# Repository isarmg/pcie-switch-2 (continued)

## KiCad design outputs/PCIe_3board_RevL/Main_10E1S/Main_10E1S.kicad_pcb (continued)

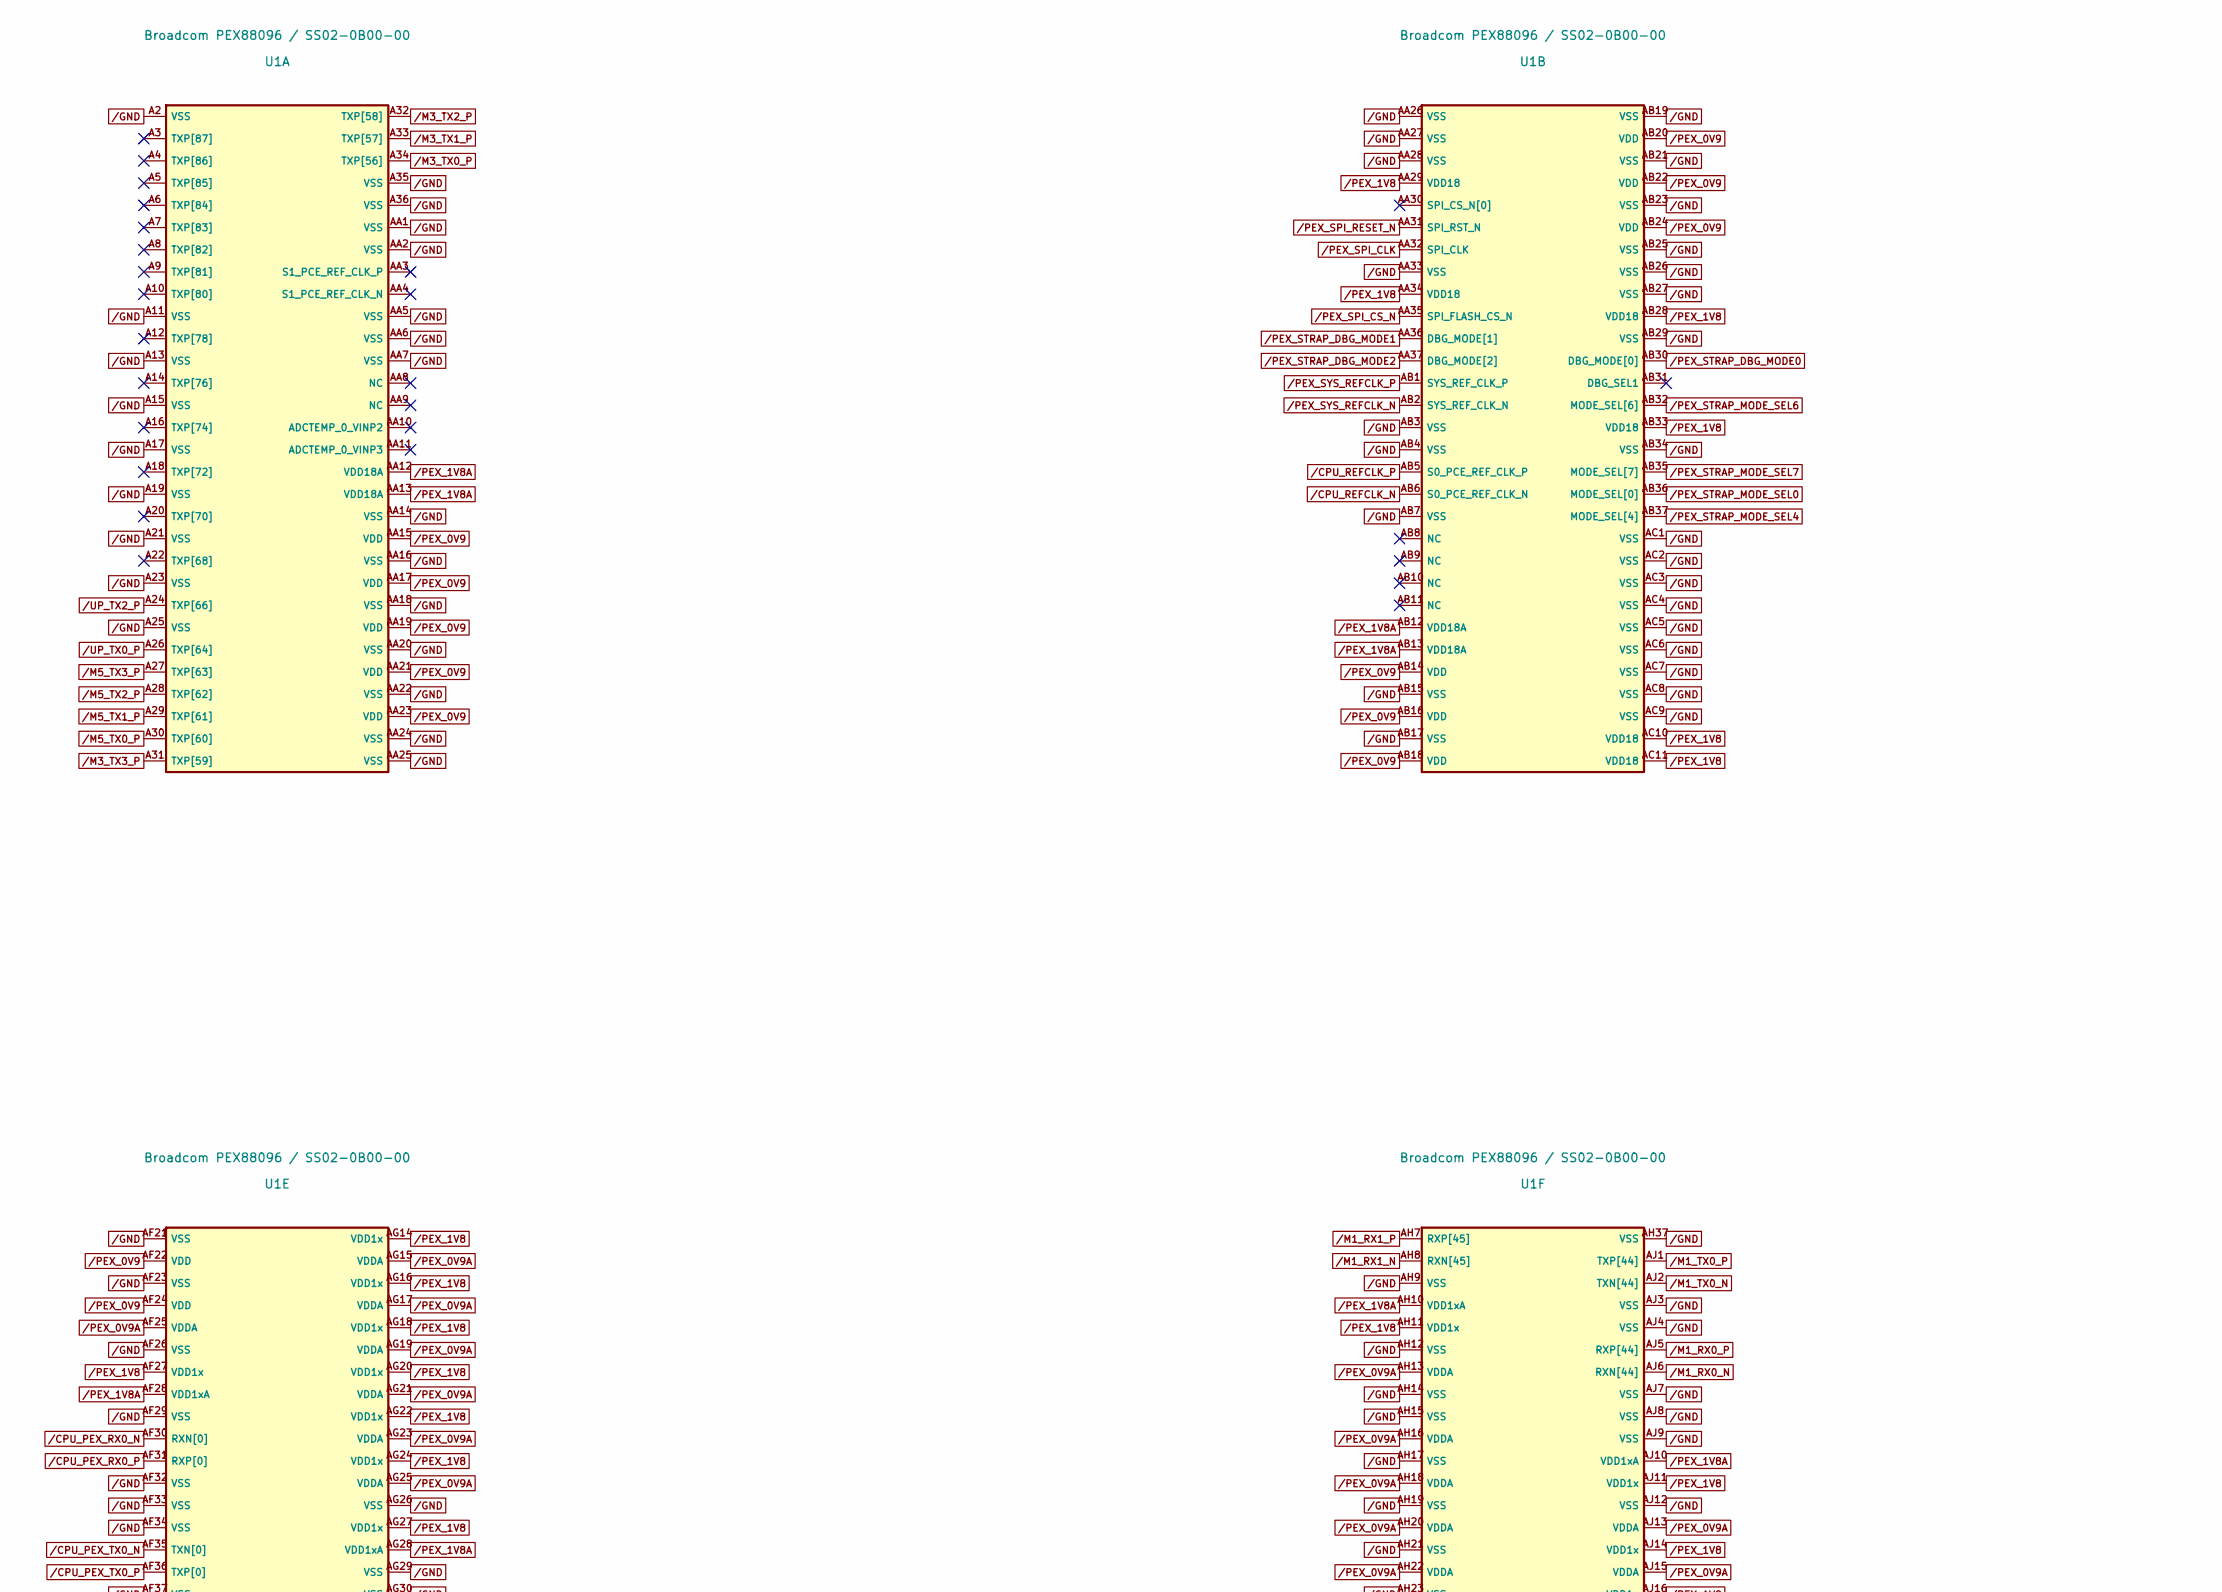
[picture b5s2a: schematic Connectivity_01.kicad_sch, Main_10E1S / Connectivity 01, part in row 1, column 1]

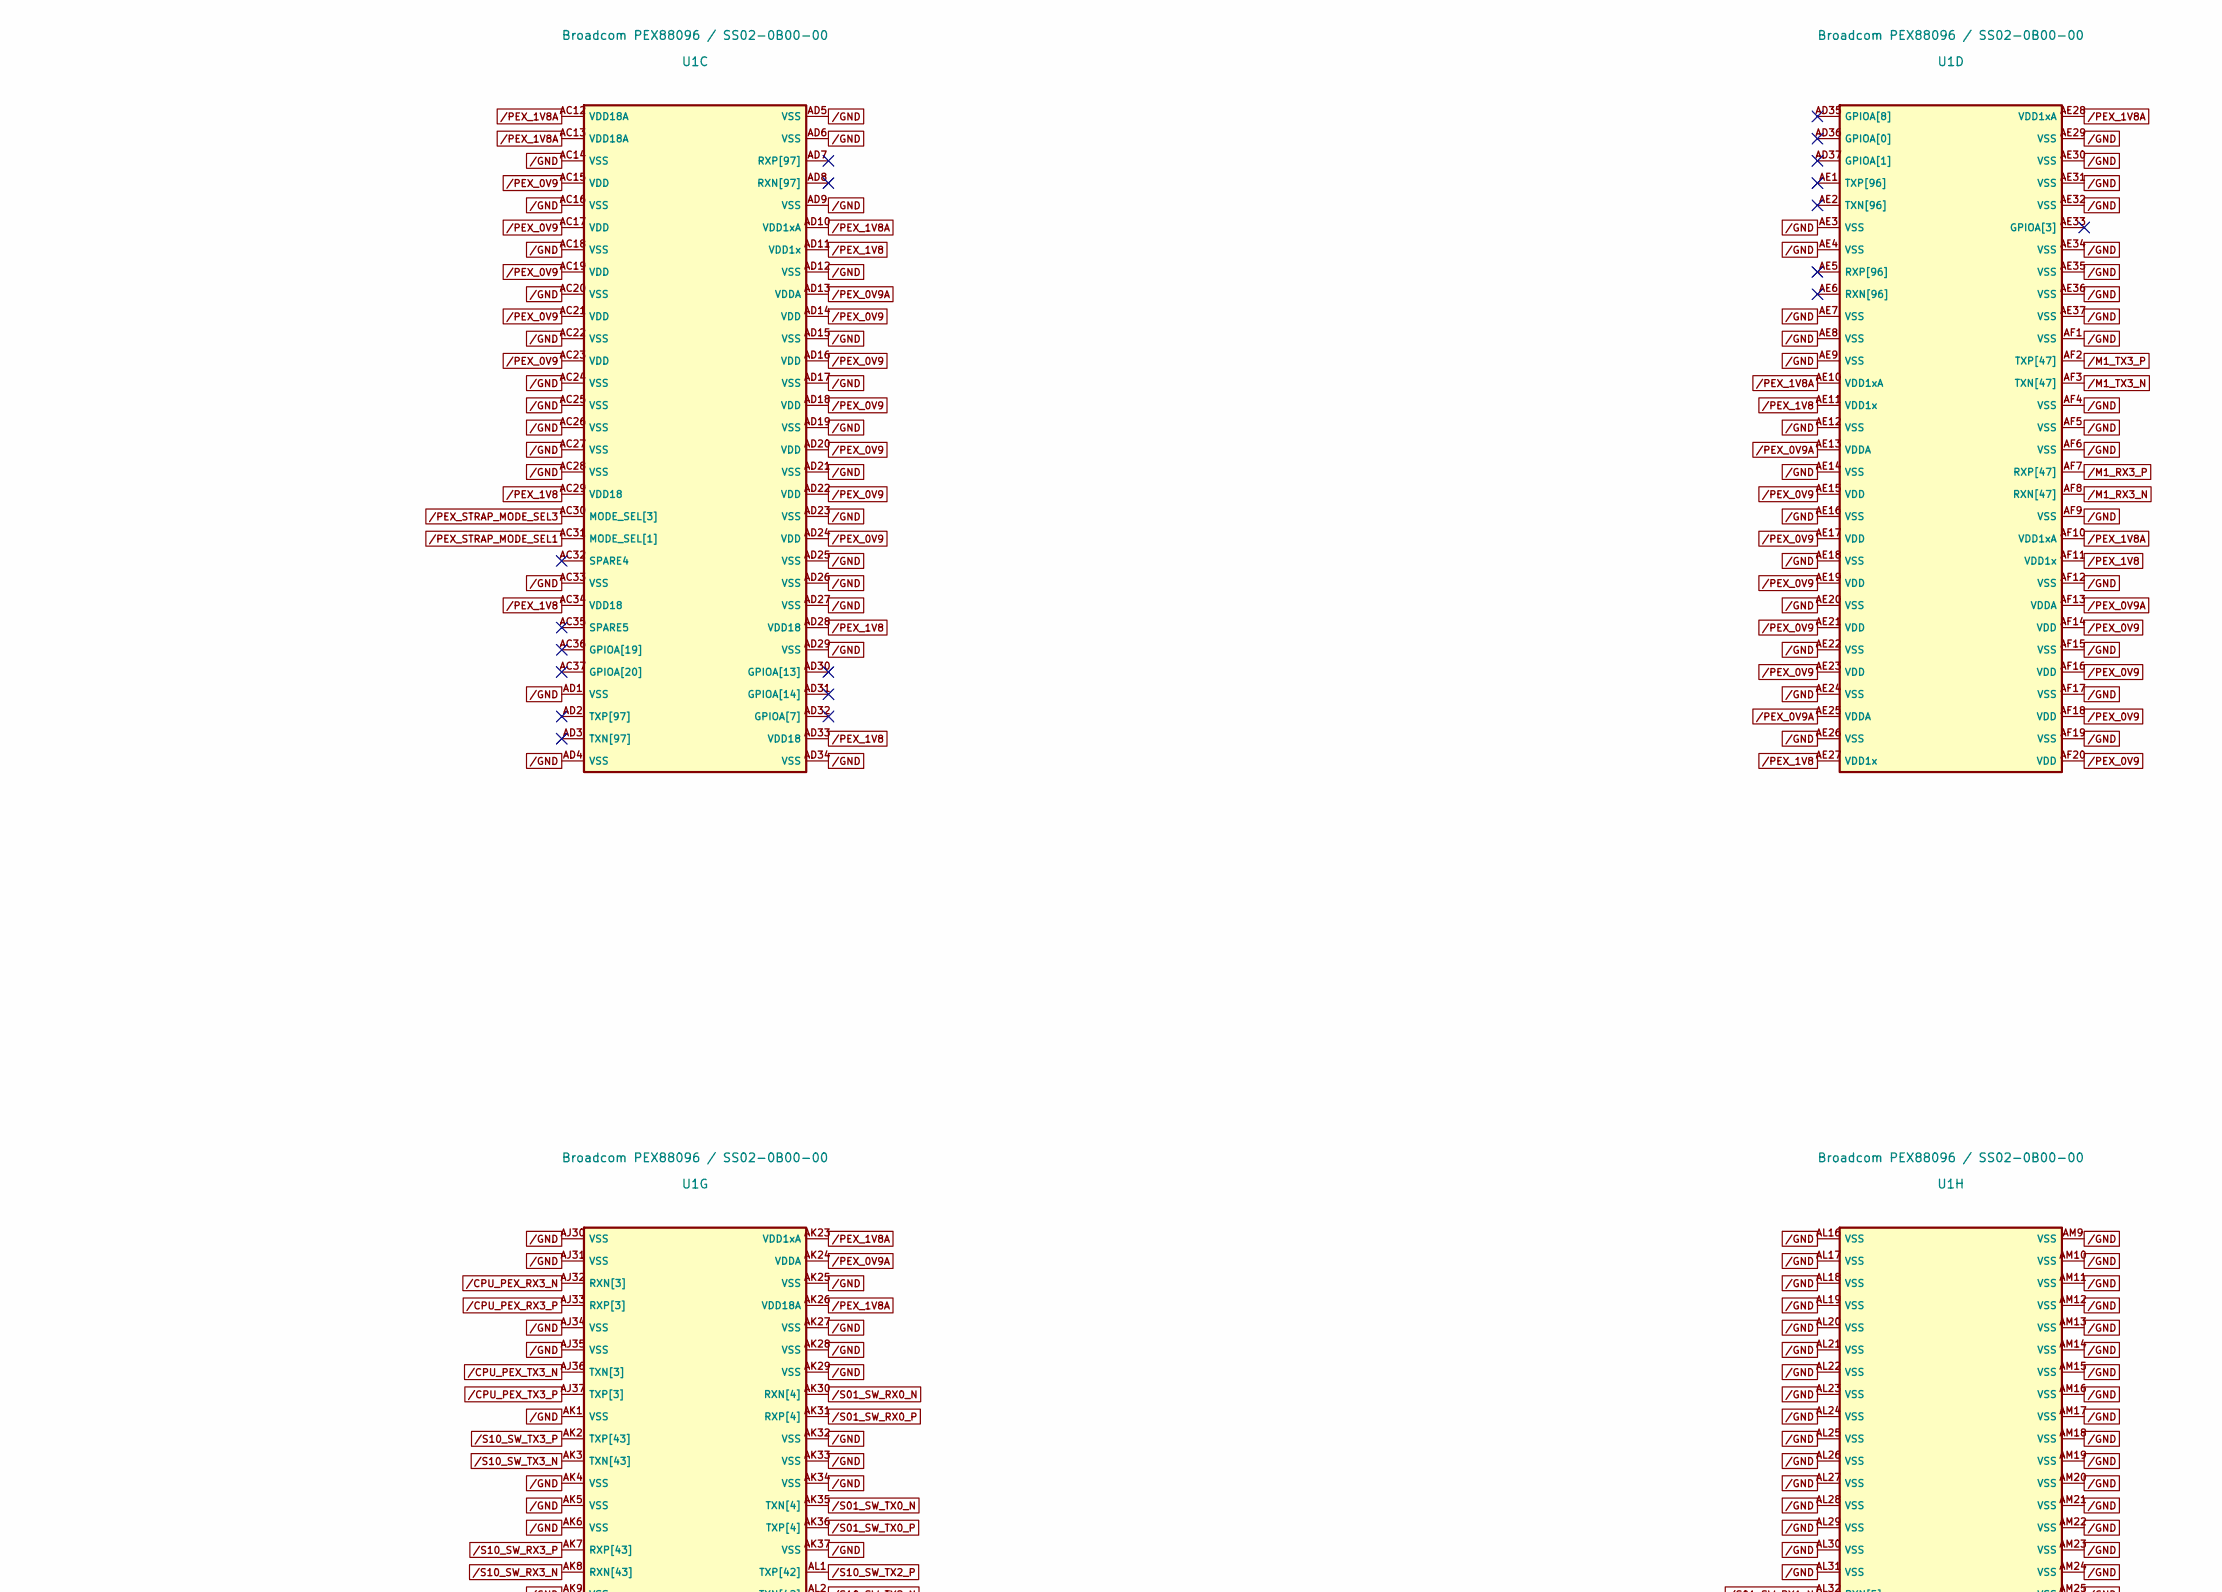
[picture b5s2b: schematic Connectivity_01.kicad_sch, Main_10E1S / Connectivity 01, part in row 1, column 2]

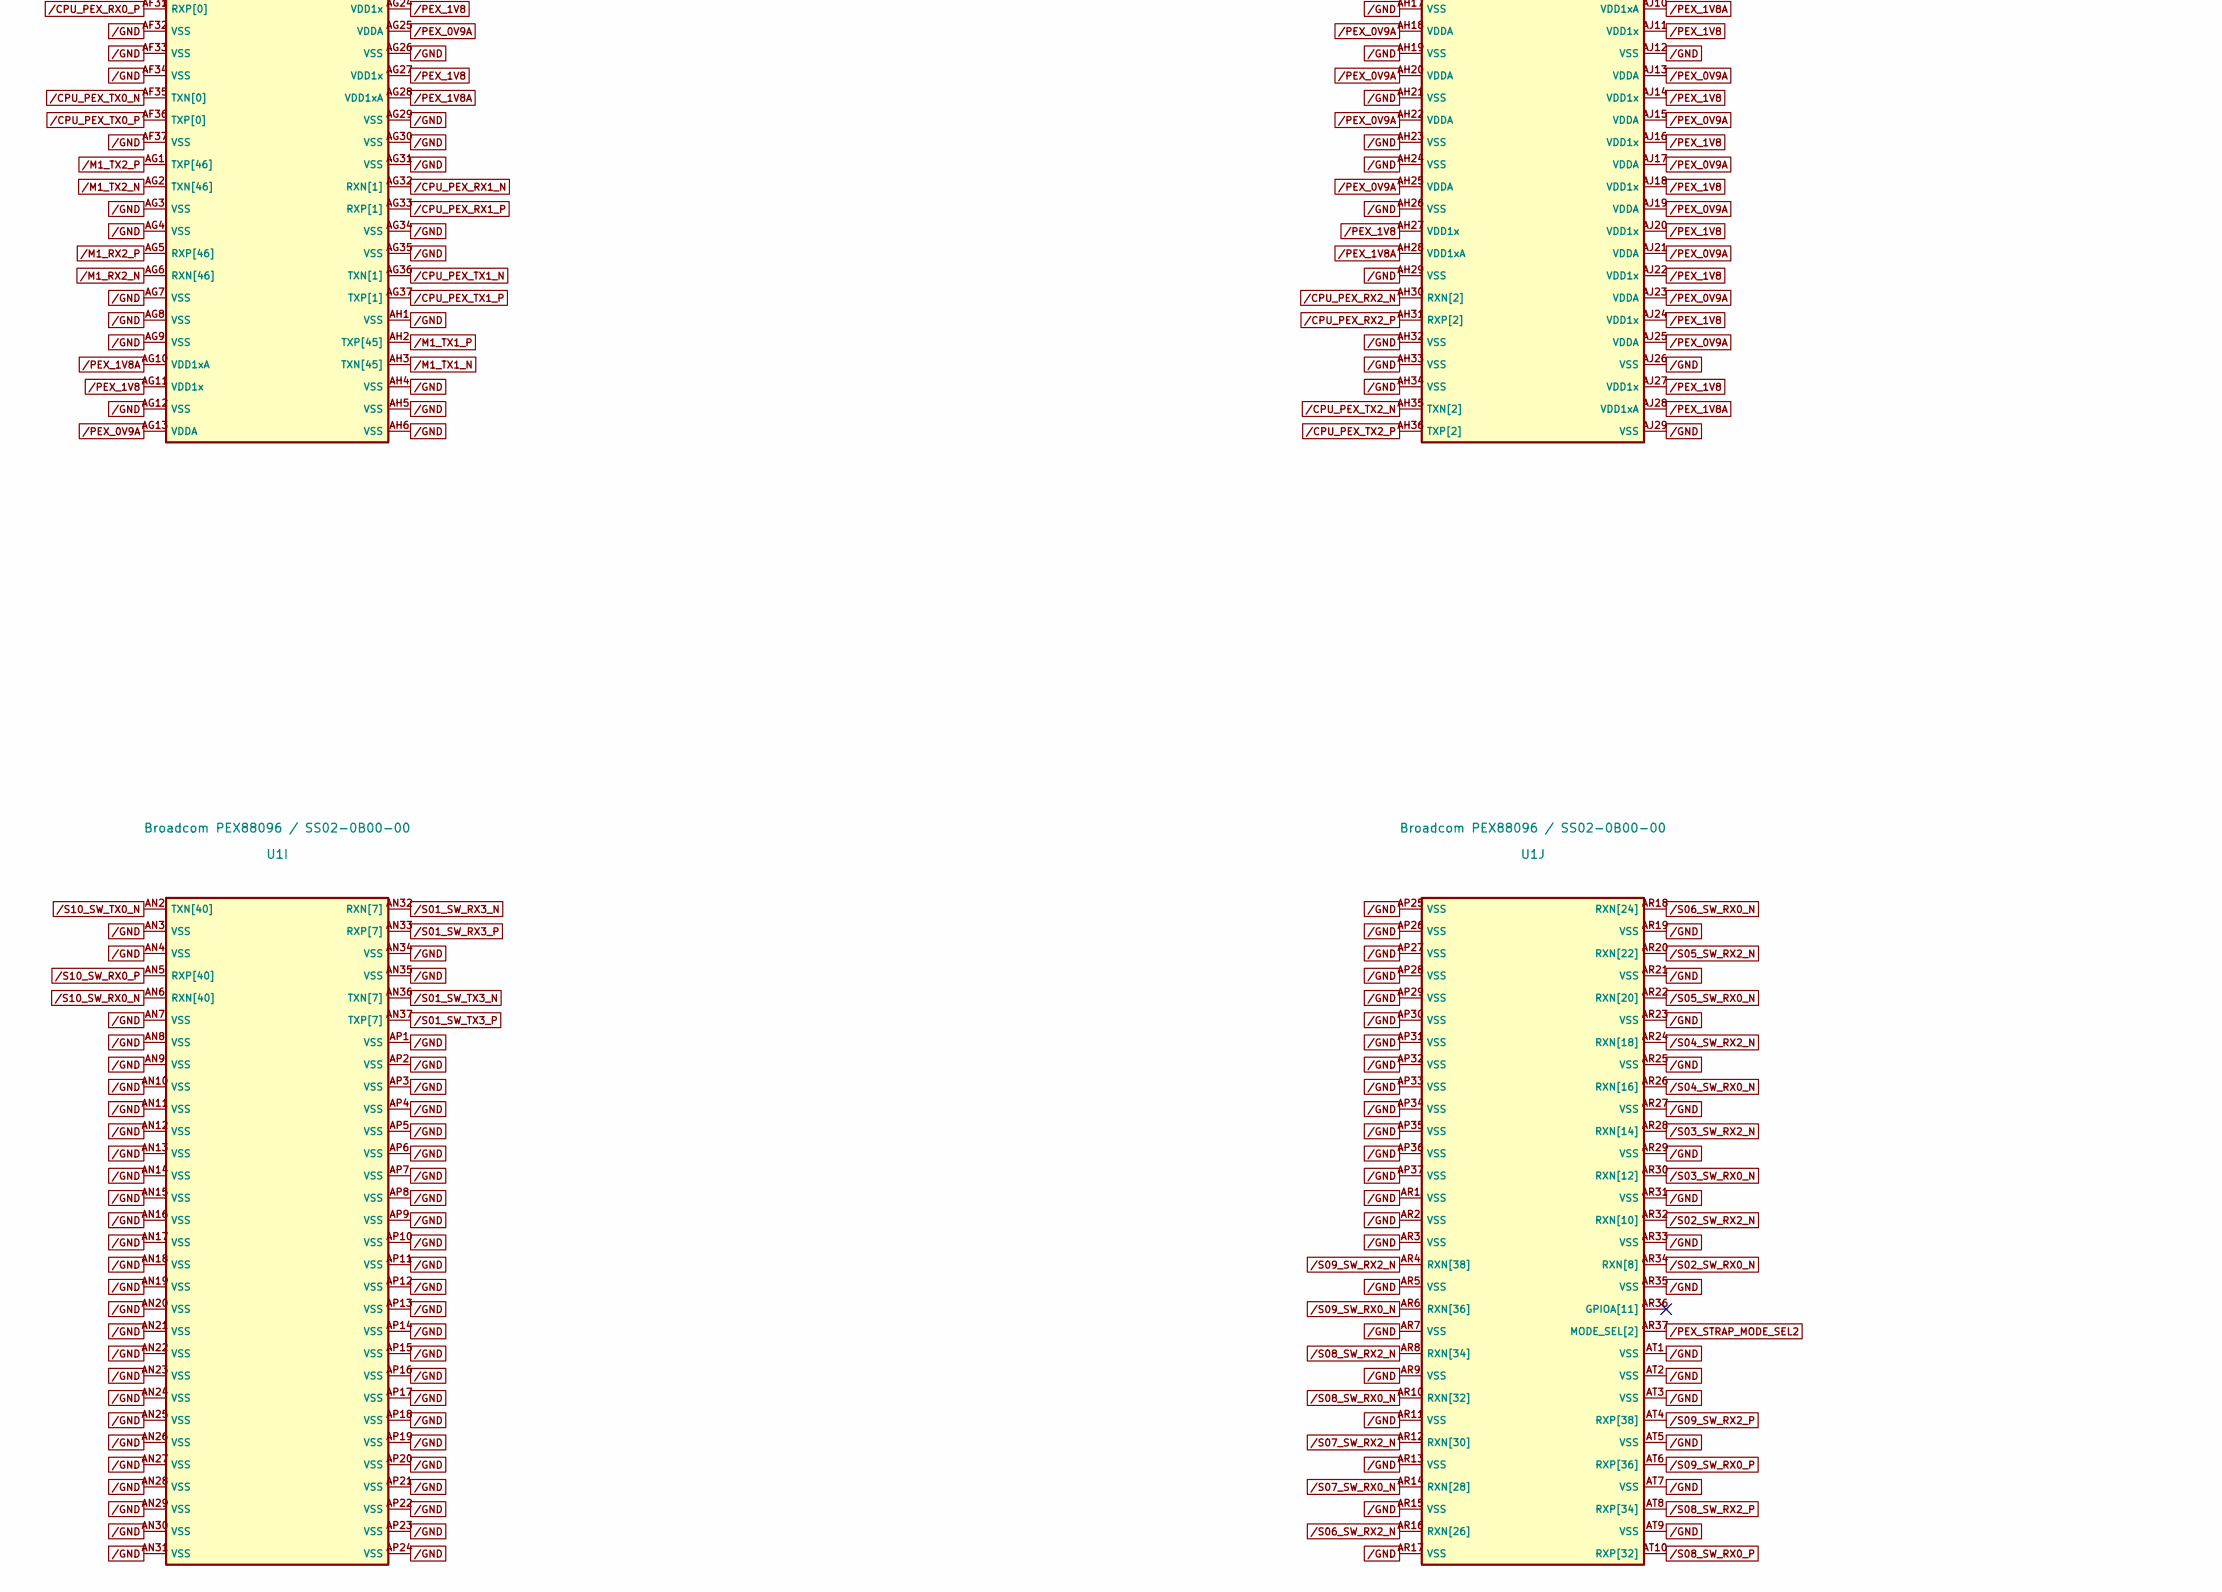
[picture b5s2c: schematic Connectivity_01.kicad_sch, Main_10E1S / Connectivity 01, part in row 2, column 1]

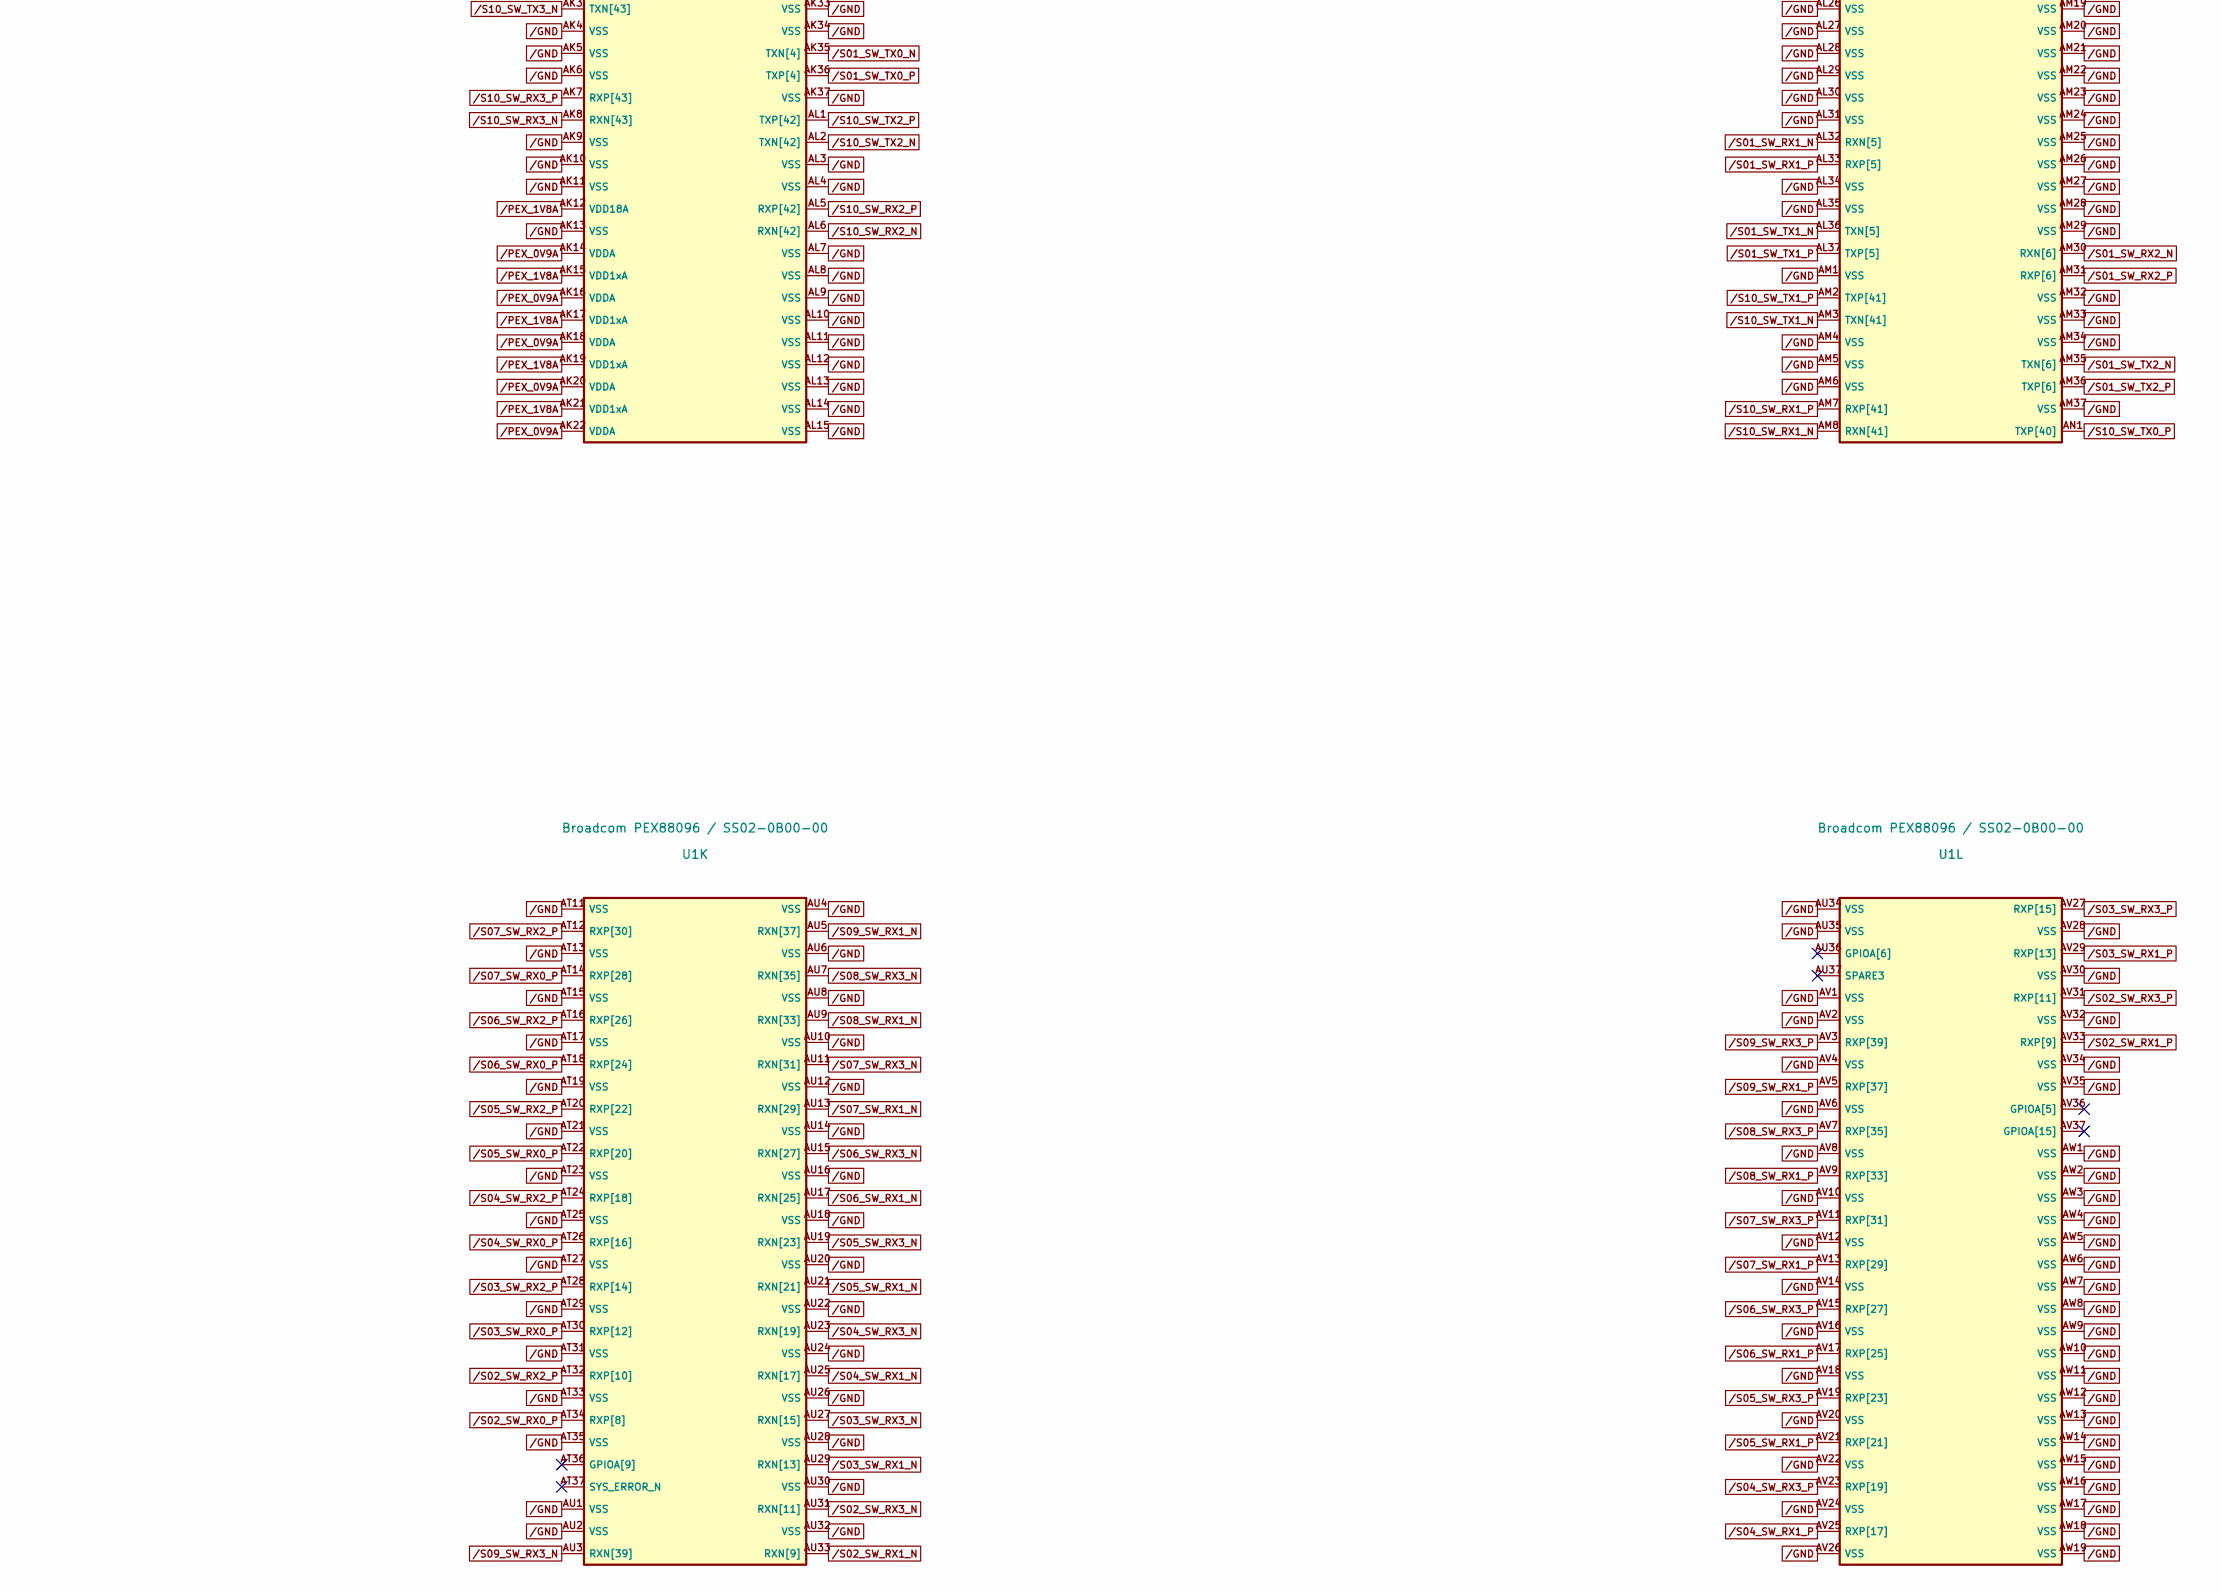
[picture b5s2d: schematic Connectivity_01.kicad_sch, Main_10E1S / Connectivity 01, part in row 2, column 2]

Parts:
U1: Broadcom PEX88096 / SS02-0B00-00; Broadcom_PEX88096_BGA1550_37p5x42p5_1mm

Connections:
/CPU_PEX_RX0_N: U1.AF30 (RXN[0]); also elsewhere on the board
/CPU_PEX_RX0_P: U1.AF31 (RXP[0]); also elsewhere on the board
/CPU_PEX_RX1_N: U1.AG32 (RXN[1]); also elsewhere on the board
/CPU_PEX_RX1_P: U1.AG33 (RXP[1]); also elsewhere on the board
/CPU_PEX_RX2_N: U1.AH30 (RXN[2]); also elsewhere on the board
/CPU_PEX_RX2_P: U1.AH31 (RXP[2]); also elsewhere on the board
/CPU_PEX_RX3_N: U1.AJ32 (RXN[3]); also elsewhere on the board
/CPU_PEX_RX3_P: U1.AJ33 (RXP[3]); also elsewhere on the board
/CPU_PEX_TX0_N: U1.AF35 (TXN[0]); also elsewhere on the board
/CPU_PEX_TX0_P: U1.AF36 (TXP[0]); also elsewhere on the board
/CPU_PEX_TX1_N: U1.AG36 (TXN[1]); also elsewhere on the board
/CPU_PEX_TX1_P: U1.AG37 (TXP[1]); also elsewhere on the board
/CPU_PEX_TX2_N: U1.AH35 (TXN[2]); also elsewhere on the board
/CPU_PEX_TX2_P: U1.AH36 (TXP[2]); also elsewhere on the board
/CPU_PEX_TX3_N: U1.AJ36 (TXN[3]); also elsewhere on the board
/CPU_PEX_TX3_P: U1.AJ37 (TXP[3]); also elsewhere on the board
/CPU_REFCLK_N: U1.AB6 (S0_PCE_REF_CLK_N); also elsewhere on the board
/CPU_REFCLK_P: U1.AB5 (S0_PCE_REF_CLK_P); also elsewhere on the board
/GND: U1.A2 (VSS), U1.A11 (VSS), U1.A13 (VSS), U1.A15 (VSS), U1.A17 (VSS), U1.A19 (VSS), U1.A21 (VSS), U1.A23 (VSS), U1.A25 (VSS), U1.A35 (VSS), U1.A36 (VSS), U1.AA1 (VSS), U1.AA2 (VSS), U1.AA5 (VSS), U1.AA6 (VSS), U1.AA7 (VSS), U1.AA14 (VSS), U1.AA16 (VSS), U1.AA18 (VSS), U1.AA20 (VSS), U1.AA22 (VSS), U1.AA24 (VSS), U1.AA25 (VSS), U1.AA26 (VSS), U1.AA27 (VSS), U1.AA28 (VSS), U1.AA33 (VSS), U1.AB3 (VSS), U1.AB4 (VSS), U1.AB7 (VSS), U1.AB15 (VSS), U1.AB17 (VSS), U1.AB19 (VSS), U1.AB21 (VSS), U1.AB23 (VSS), U1.AB25 (VSS), U1.AB26 (VSS), U1.AB27 (VSS), U1.AB29 (VSS), U1.AB34 (VSS), U1.AC1 (VSS), U1.AC2 (VSS), U1.AC3 (VSS), U1.AC4 (VSS), U1.AC5 (VSS), U1.AC6 (VSS), U1.AC7 (VSS), U1.AC8 (VSS), U1.AC9 (VSS), U1.AC14 (VSS), U1.AC16 (VSS), U1.AC18 (VSS), U1.AC20 (VSS), U1.AC22 (VSS), U1.AC24 (VSS), U1.AC25 (VSS), U1.AC26 (VSS), U1.AC27 (VSS), U1.AC28 (VSS), U1.AC33 (VSS), U1.AD1 (VSS), U1.AD4 (VSS), U1.AD5 (VSS), U1.AD6 (VSS), U1.AD9 (VSS), U1.AD12 (VSS), U1.AD15 (VSS), U1.AD17 (VSS), U1.AD19 (VSS), U1.AD21 (VSS), U1.AD23 (VSS), U1.AD25 (VSS), U1.AD26 (VSS), U1.AD27 (VSS), U1.AD29 (VSS), U1.AD34 (VSS), U1.AE3 (VSS), U1.AE4 (VSS), U1.AE7 (VSS), U1.AE8 (VSS), U1.AE9 (VSS), U1.AE12 (VSS), U1.AE14 (VSS), U1.AE16 (VSS), U1.AE18 (VSS), U1.AE20 (VSS), U1.AE22 (VSS), U1.AE24 (VSS), U1.AE26 (VSS), U1.AE29 (VSS), U1.AE30 (VSS), U1.AE31 (VSS), U1.AE32 (VSS), U1.AE34 (VSS), U1.AE35 (VSS), U1.AE36 (VSS), U1.AE37 (VSS), U1.AF1 (VSS), U1.AF4 (VSS), U1.AF5 (VSS), U1.AF6 (VSS), U1.AF9 (VSS), U1.AF12 (VSS), U1.AF15 (VSS), U1.AF17 (VSS), U1.AF19 (VSS), U1.AF21 (VSS), U1.AF23 (VSS), U1.AF26 (VSS), U1.AF29 (VSS), U1.AF32 (VSS), U1.AF33 (VSS), U1.AF34 (VSS), U1.AF37 (VSS), U1.AG3 (VSS), U1.AG4 (VSS), U1.AG7 (VSS), U1.AG8 (VSS), U1.AG9 (VSS), U1.AG12 (VSS), U1.AG26 (VSS), U1.AG29 (VSS), U1.AG30 (VSS), U1.AG31 (VSS), U1.AG34 (VSS), U1.AG35 (VSS), U1.AH1 (VSS), U1.AH4 (VSS), U1.AH5 (VSS), U1.AH6 (VSS), U1.AH9 (VSS), U1.AH12 (VSS), U1.AH14 (VSS), U1.AH15 (VSS), U1.AH17 (VSS), U1.AH19 (VSS), U1.AH21 (VSS), U1.AH23 (VSS), U1.AH24 (VSS), U1.AH26 (VSS), U1.AH29 (VSS), U1.AH32 (VSS), U1.AH33 (VSS), U1.AH34 (VSS), U1.AH37 (VSS), U1.AJ3 (VSS), U1.AJ4 (VSS), U1.AJ7 (VSS), U1.AJ8 (VSS), U1.AJ9 (VSS), U1.AJ12 (VSS), U1.AJ26 (VSS), U1.AJ29 (VSS), U1.AJ30 (VSS), U1.AJ31 (VSS), U1.AJ34 (VSS), U1.AJ35 (VSS), U1.AK1 (VSS), U1.AK4 (VSS), U1.AK5 (VSS), U1.AK6 (VSS), U1.AK9 (VSS), U1.AK10 (VSS), U1.AK11 (VSS), U1.AK13 (VSS), U1.AK25 (VSS), U1.AK27 (VSS), U1.AK28 (VSS), U1.AK29 (VSS), U1.AK32 (VSS), U1.AK33 (VSS), U1.AK34 (VSS), U1.AK37 (VSS), U1.AL3 (VSS), U1.AL4 (VSS), U1.AL7 (VSS), U1.AL8 (VSS), U1.AL9 (VSS), U1.AL10 (VSS), U1.AL11 (VSS), U1.AL12 (VSS), U1.AL13 (VSS), U1.AL14 (VSS), U1.AL15 (VSS), U1.AL16 (VSS), U1.AL17 (VSS), U1.AL18 (VSS), U1.AL19 (VSS), U1.AL20 (VSS), U1.AL21 (VSS), U1.AL22 (VSS), U1.AL23 (VSS), U1.AL24 (VSS), U1.AL25 (VSS), U1.AL26 (VSS), U1.AL27 (VSS), U1.AL28 (VSS), U1.AL29 (VSS), U1.AL30 (VSS), U1.AL31 (VSS), U1.AL34 (VSS), U1.AL35 (VSS), U1.AM1 (VSS), U1.AM4 (VSS), U1.AM5 (VSS), U1.AM6 (VSS), U1.AM9 (VSS), U1.AM10 (VSS), U1.AM11 (VSS), U1.AM12 (VSS), U1.AM13 (VSS), U1.AM14 (VSS), U1.AM15 (VSS), U1.AM16 (VSS), U1.AM17 (VSS), U1.AM18 (VSS), U1.AM19 (VSS), U1.AM20 (VSS), U1.AM21 (VSS), U1.AM22 (VSS), U1.AM23 (VSS), U1.AM24 (VSS), U1.AM25 (VSS), U1.AM26 (VSS), U1.AM27 (VSS), U1.AM28 (VSS), U1.AM29 (VSS), U1.AM32 (VSS), U1.AM33 (VSS), U1.AM34 (VSS), U1.AM37 (VSS), U1.AN3 (VSS), U1.AN4 (VSS), U1.AN7 (VSS), U1.AN8 (VSS), U1.AN9 (VSS), U1.AN10 (VSS), U1.AN11 (VSS), U1.AN12 (VSS), U1.AN13 (VSS), U1.AN14 (VSS), U1.AN15 (VSS), U1.AN16 (VSS), U1.AN17 (VSS), U1.AN18 (VSS), U1.AN19 (VSS), U1.AN20 (VSS), U1.AN21 (VSS), U1.AN22 (VSS), U1.AN23 (VSS), U1.AN24 (VSS), U1.AN25 (VSS), U1.AN26 (VSS), U1.AN27 (VSS), U1.AN28 (VSS), U1.AN29 (VSS), U1.AN30 (VSS), U1.AN31 (VSS), U1.AN34 (VSS), U1.AN35 (VSS), U1.AP1 (VSS), U1.AP2 (VSS), U1.AP3 (VSS), U1.AP4 (VSS), U1.AP5 (VSS), U1.AP6 (VSS), U1.AP7 (VSS), U1.AP8 (VSS), U1.AP9 (VSS), U1.AP10 (VSS), U1.AP11 (VSS), U1.AP12 (VSS), U1.AP13 (VSS), U1.AP14 (VSS), U1.AP15 (VSS), U1.AP16 (VSS), U1.AP17 (VSS), U1.AP18 (VSS), U1.AP19 (VSS), U1.AP20 (VSS), U1.AP21 (VSS), U1.AP22 (VSS), U1.AP23 (VSS), U1.AP24 (VSS), U1.AP25 (VSS), U1.AP26 (VSS), U1.AP27 (VSS), U1.AP28 (VSS), U1.AP29 (VSS), U1.AP30 (VSS), U1.AP31 (VSS), U1.AP32 (VSS), U1.AP33 (VSS), U1.AP34 (VSS), U1.AP35 (VSS), U1.AP36 (VSS), U1.AP37 (VSS), U1.AR1 (VSS), U1.AR2 (VSS), U1.AR3 (VSS), U1.AR5 (VSS), U1.AR7 (VSS), U1.AR9 (VSS), U1.AR11 (VSS), U1.AR13 (VSS), U1.AR15 (VSS), U1.AR17 (VSS), U1.AR19 (VSS), U1.AR21 (VSS), U1.AR23 (VSS), U1.AR25 (VSS), U1.AR27 (VSS), U1.AR29 (VSS), U1.AR31 (VSS), U1.AR33 (VSS), U1.AR35 (VSS), U1.AT1 (VSS), U1.AT2 (VSS), U1.AT3 (VSS), U1.AT5 (VSS), U1.AT7 (VSS), U1.AT9 (VSS), U1.AT11 (VSS), U1.AT13 (VSS), U1.AT15 (VSS), U1.AT17 (VSS), U1.AT19 (VSS), U1.AT21 (VSS), U1.AT23 (VSS), U1.AT25 (VSS), U1.AT27 (VSS), U1.AT29 (VSS), U1.AT31 (VSS), U1.AT33 (VSS), U1.AT35 (VSS), U1.AU1 (VSS), U1.AU2 (VSS), U1.AU4 (VSS), U1.AU6 (VSS), U1.AU8 (VSS), U1.AU10 (VSS), U1.AU12 (VSS), U1.AU14 (VSS), U1.AU16 (VSS), U1.AU18 (VSS), U1.AU20 (VSS), U1.AU22 (VSS), U1.AU24 (VSS), U1.AU26 (VSS), U1.AU28 (VSS), U1.AU30 (VSS), U1.AU32 (VSS), U1.AU34 (VSS), U1.AU35 (VSS), U1.AV1 (VSS), U1.AV2 (VSS), U1.AV4 (VSS), U1.AV6 (VSS), U1.AV8 (VSS), U1.AV10 (VSS), U1.AV12 (VSS), U1.AV14 (VSS), U1.AV16 (VSS), U1.AV18 (VSS), U1.AV20 (VSS), U1.AV22 (VSS), U1.AV24 (VSS), U1.AV26 (VSS), U1.AV28 (VSS), U1.AV30 (VSS), U1.AV32 (VSS), U1.AV34 (VSS), U1.AV35 (VSS), U1.AW1 (VSS), U1.AW2 (VSS), U1.AW3 (VSS), U1.AW4 (VSS), U1.AW5 (VSS), U1.AW6 (VSS), U1.AW7 (VSS), U1.AW8 (VSS), U1.AW9 (VSS), U1.AW10 (VSS), U1.AW11 (VSS), U1.AW12 (VSS), U1.AW13 (VSS), U1.AW14 (VSS), U1.AW15 (VSS), U1.AW16 (VSS), U1.AW17 (VSS), U1.AW18 (VSS), U1.AW19 (VSS); also elsewhere on the board
/M1_RX0_N: U1.AJ6 (RXN[44]); also elsewhere on the board
/M1_RX0_P: U1.AJ5 (RXP[44]); also elsewhere on the board
/M1_RX1_N: U1.AH8 (RXN[45]); also elsewhere on the board
/M1_RX1_P: U1.AH7 (RXP[45]); also elsewhere on the board
/M1_RX2_N: U1.AG6 (RXN[46]); also elsewhere on the board
/M1_RX2_P: U1.AG5 (RXP[46]); also elsewhere on the board
/M1_RX3_N: U1.AF8 (RXN[47]); also elsewhere on the board
/M1_RX3_P: U1.AF7 (RXP[47]); also elsewhere on the board
/M1_TX0_N: U1.AJ2 (TXN[44]); also elsewhere on the board
/M1_TX0_P: U1.AJ1 (TXP[44]); also elsewhere on the board
/M1_TX1_N: U1.AH3 (TXN[45]); also elsewhere on the board
/M1_TX1_P: U1.AH2 (TXP[45]); also elsewhere on the board
/M1_TX2_N: U1.AG2 (TXN[46]); also elsewhere on the board
/M1_TX2_P: U1.AG1 (TXP[46]); also elsewhere on the board
/M1_TX3_N: U1.AF3 (TXN[47]); also elsewhere on the board
/M1_TX3_P: U1.AF2 (TXP[47]); also elsewhere on the board
/M3_TX0_P: U1.A34 (TXP[56]); also elsewhere on the board
/M3_TX1_P: U1.A33 (TXP[57]); also elsewhere on the board
/M3_TX2_P: U1.A32 (TXP[58]); also elsewhere on the board
/M3_TX3_P: U1.A31 (TXP[59]); also elsewhere on the board
/M5_TX0_P: U1.A30 (TXP[60]); also elsewhere on the board
/M5_TX1_P: U1.A29 (TXP[61]); also elsewhere on the board
/M5_TX2_P: U1.A28 (TXP[62]); also elsewhere on the board
/M5_TX3_P: U1.A27 (TXP[63]); also elsewhere on the board
/PEX_0V9: U1.AA15 (VDD), U1.AA17 (VDD), U1.AA19 (VDD), U1.AA21 (VDD), U1.AA23 (VDD), U1.AB14 (VDD), U1.AB16 (VDD), U1.AB18 (VDD), U1.AB20 (VDD), U1.AB22 (VDD), U1.AB24 (VDD), U1.AC15 (VDD), U1.AC17 (VDD), U1.AC19 (VDD), U1.AC21 (VDD), U1.AC23 (VDD), U1.AD14 (VDD), U1.AD16 (VDD), U1.AD18 (VDD), U1.AD20 (VDD), U1.AD22 (VDD), U1.AD24 (VDD), U1.AE15 (VDD), U1.AE17 (VDD), U1.AE19 (VDD), U1.AE21 (VDD), U1.AE23 (VDD), U1.AF14 (VDD), U1.AF16 (VDD), U1.AF18 (VDD), U1.AF20 (VDD), U1.AF22 (VDD), U1.AF24 (VDD); also elsewhere on the board
/PEX_0V9A: U1.AD13 (VDDA), U1.AE13 (VDDA), U1.AE25 (VDDA), U1.AF13 (VDDA), U1.AF25 (VDDA), U1.AG13 (VDDA), U1.AG15 (VDDA), U1.AG17 (VDDA), U1.AG19 (VDDA), U1.AG21 (VDDA), U1.AG23 (VDDA), U1.AG25 (VDDA), U1.AH13 (VDDA), U1.AH16 (VDDA), U1.AH18 (VDDA), U1.AH20 (VDDA), U1.AH22 (VDDA), U1.AH25 (VDDA), U1.AJ13 (VDDA), U1.AJ15 (VDDA), U1.AJ17 (VDDA), U1.AJ19 (VDDA), U1.AJ21 (VDDA), U1.AJ23 (VDDA), U1.AJ25 (VDDA), U1.AK14 (VDDA), U1.AK16 (VDDA), U1.AK18 (VDDA), U1.AK20 (VDDA), U1.AK22 (VDDA), U1.AK24 (VDDA); also elsewhere on the board
/PEX_1V8: U1.AA29 (VDD18), U1.AA34 (VDD18), U1.AB28 (VDD18), U1.AB33 (VDD18), U1.AC10 (VDD18), U1.AC11 (VDD18), U1.AC29 (VDD18), U1.AC34 (VDD18), U1.AD11 (VDD1x), U1.AD28 (VDD18), U1.AD33 (VDD18), U1.AE11 (VDD1x), U1.AE27 (VDD1x), U1.AF11 (VDD1x), U1.AF27 (VDD1x), U1.AG11 (VDD1x), U1.AG14 (VDD1x), U1.AG16 (VDD1x), U1.AG18 (VDD1x), U1.AG20 (VDD1x), U1.AG22 (VDD1x), U1.AG24 (VDD1x), U1.AG27 (VDD1x), U1.AH11 (VDD1x), U1.AH27 (VDD1x), U1.AJ11 (VDD1x), U1.AJ14 (VDD1x), U1.AJ16 (VDD1x), U1.AJ18 (VDD1x), U1.AJ20 (VDD1x), U1.AJ22 (VDD1x), U1.AJ24 (VDD1x), U1.AJ27 (VDD1x); also elsewhere on the board
/PEX_1V8A: U1.AA12 (VDD18A), U1.AA13 (VDD18A), U1.AB12 (VDD18A), U1.AB13 (VDD18A), U1.AC12 (VDD18A), U1.AC13 (VDD18A), U1.AD10 (VDD1xA), U1.AE10 (VDD1xA), U1.AE28 (VDD1xA), U1.AF10 (VDD1xA), U1.AF28 (VDD1xA), U1.AG10 (VDD1xA), U1.AG28 (VDD1xA), U1.AH10 (VDD1xA), U1.AH28 (VDD1xA), U1.AJ10 (VDD1xA), U1.AJ28 (VDD1xA), U1.AK12 (VDD18A), U1.AK15 (VDD1xA), U1.AK17 (VDD1xA), U1.AK19 (VDD1xA), U1.AK21 (VDD1xA), U1.AK23 (VDD1xA), U1.AK26 (VDD18A); also elsewhere on the board
/PEX_SPI_CLK: U1.AA32 (SPI_CLK); also elsewhere on the board
/PEX_SPI_CS_N: U1.AA35 (SPI_FLASH_CS_N); also elsewhere on the board
/PEX_SPI_RESET_N: U1.AA31 (SPI_RST_N)
/PEX_STRAP_DBG_MODE0: U1.AB30 (DBG_MODE[0])
/PEX_STRAP_DBG_MODE1: U1.AA36 (DBG_MODE[1])
/PEX_STRAP_DBG_MODE2: U1.AA37 (DBG_MODE[2])
/PEX_STRAP_MODE_SEL0: U1.AB36 (MODE_SEL[0])
/PEX_STRAP_MODE_SEL1: U1.AC31 (MODE_SEL[1])
/PEX_STRAP_MODE_SEL2: U1.AR37 (MODE_SEL[2])
/PEX_STRAP_MODE_SEL3: U1.AC30 (MODE_SEL[3])
/PEX_STRAP_MODE_SEL4: U1.AB37 (MODE_SEL[4])
/PEX_STRAP_MODE_SEL6: U1.AB32 (MODE_SEL[6])
/PEX_STRAP_MODE_SEL7: U1.AB35 (MODE_SEL[7])
/PEX_SYS_REFCLK_N: U1.AB2 (SYS_REF_CLK_N); also elsewhere on the board
/PEX_SYS_REFCLK_P: U1.AB1 (SYS_REF_CLK_P); also elsewhere on the board
/S01_SW_RX0_N: U1.AK30 (RXN[4]); also elsewhere on the board
/S01_SW_RX0_P: U1.AK31 (RXP[4]); also elsewhere on the board
/S01_SW_RX1_N: U1.AL32 (RXN[5]); also elsewhere on the board
/S01_SW_RX1_P: U1.AL33 (RXP[5]); also elsewhere on the board
/S01_SW_RX2_N: U1.AM30 (RXN[6]); also elsewhere on the board
/S01_SW_RX2_P: U1.AM31 (RXP[6]); also elsewhere on the board
/S01_SW_RX3_N: U1.AN32 (RXN[7]); also elsewhere on the board
/S01_SW_RX3_P: U1.AN33 (RXP[7]); also elsewhere on the board
/S01_SW_TX0_N: U1.AK35 (TXN[4]); also elsewhere on the board
/S01_SW_TX0_P: U1.AK36 (TXP[4]); also elsewhere on the board
/S01_SW_TX1_N: U1.AL36 (TXN[5]); also elsewhere on the board
/S01_SW_TX1_P: U1.AL37 (TXP[5]); also elsewhere on the board
/S01_SW_TX2_N: U1.AM35 (TXN[6]); also elsewhere on the board
/S01_SW_TX2_P: U1.AM36 (TXP[6]); also elsewhere on the board
/S01_SW_TX3_N: U1.AN36 (TXN[7]); also elsewhere on the board
/S01_SW_TX3_P: U1.AN37 (TXP[7]); also elsewhere on the board
/S02_SW_RX0_N: U1.AR34 (RXN[8]); also elsewhere on the board
/S02_SW_RX0_P: U1.AT34 (RXP[8]); also elsewhere on the board
/S02_SW_RX1_N: U1.AU33 (RXN[9]); also elsewhere on the board
/S02_SW_RX1_P: U1.AV33 (RXP[9]); also elsewhere on the board
/S02_SW_RX2_N: U1.AR32 (RXN[10]); also elsewhere on the board
/S02_SW_RX2_P: U1.AT32 (RXP[10]); also elsewhere on the board
/S02_SW_RX3_N: U1.AU31 (RXN[11]); also elsewhere on the board
/S02_SW_RX3_P: U1.AV31 (RXP[11]); also elsewhere on the board
/S03_SW_RX0_N: U1.AR30 (RXN[12]); also elsewhere on the board
/S03_SW_RX0_P: U1.AT30 (RXP[12]); also elsewhere on the board
/S03_SW_RX1_N: U1.AU29 (RXN[13]); also elsewhere on the board
/S03_SW_RX1_P: U1.AV29 (RXP[13]); also elsewhere on the board
/S03_SW_RX2_N: U1.AR28 (RXN[14]); also elsewhere on the board
/S03_SW_RX2_P: U1.AT28 (RXP[14]); also elsewhere on the board
/S03_SW_RX3_N: U1.AU27 (RXN[15]); also elsewhere on the board
/S03_SW_RX3_P: U1.AV27 (RXP[15]); also elsewhere on the board
/S04_SW_RX0_N: U1.AR26 (RXN[16]); also elsewhere on the board
/S04_SW_RX0_P: U1.AT26 (RXP[16]); also elsewhere on the board
/S04_SW_RX1_N: U1.AU25 (RXN[17]); also elsewhere on the board
/S04_SW_RX1_P: U1.AV25 (RXP[17]); also elsewhere on the board
/S04_SW_RX2_N: U1.AR24 (RXN[18]); also elsewhere on the board
/S04_SW_RX2_P: U1.AT24 (RXP[18]); also elsewhere on the board
/S04_SW_RX3_N: U1.AU23 (RXN[19]); also elsewhere on the board
/S04_SW_RX3_P: U1.AV23 (RXP[19]); also elsewhere on the board
/S05_SW_RX0_N: U1.AR22 (RXN[20]); also elsewhere on the board
/S05_SW_RX0_P: U1.AT22 (RXP[20]); also elsewhere on the board
/S05_SW_RX1_N: U1.AU21 (RXN[21]); also elsewhere on the board
/S05_SW_RX1_P: U1.AV21 (RXP[21]); also elsewhere on the board
/S05_SW_RX2_N: U1.AR20 (RXN[22]); also elsewhere on the board
/S05_SW_RX2_P: U1.AT20 (RXP[22]); also elsewhere on the board
/S05_SW_RX3_N: U1.AU19 (RXN[23]); also elsewhere on the board
/S05_SW_RX3_P: U1.AV19 (RXP[23]); also elsewhere on the board
/S06_SW_RX0_N: U1.AR18 (RXN[24]); also elsewhere on the board
/S06_SW_RX0_P: U1.AT18 (RXP[24]); also elsewhere on the board
/S06_SW_RX1_N: U1.AU17 (RXN[25]); also elsewhere on the board
/S06_SW_RX1_P: U1.AV17 (RXP[25]); also elsewhere on the board
/S06_SW_RX2_N: U1.AR16 (RXN[26]); also elsewhere on the board
/S06_SW_RX2_P: U1.AT16 (RXP[26]); also elsewhere on the board
/S06_SW_RX3_N: U1.AU15 (RXN[27]); also elsewhere on the board
/S06_SW_RX3_P: U1.AV15 (RXP[27]); also elsewhere on the board
/S07_SW_RX0_N: U1.AR14 (RXN[28]); also elsewhere on the board
/S07_SW_RX0_P: U1.AT14 (RXP[28]); also elsewhere on the board
/S07_SW_RX1_N: U1.AU13 (RXN[29]); also elsewhere on the board
/S07_SW_RX1_P: U1.AV13 (RXP[29]); also elsewhere on the board
/S07_SW_RX2_N: U1.AR12 (RXN[30]); also elsewhere on the board
/S07_SW_RX2_P: U1.AT12 (RXP[30]); also elsewhere on the board
/S07_SW_RX3_N: U1.AU11 (RXN[31]); also elsewhere on the board
/S07_SW_RX3_P: U1.AV11 (RXP[31]); also elsewhere on the board
/S08_SW_RX0_N: U1.AR10 (RXN[32]); also elsewhere on the board
/S08_SW_RX0_P: U1.AT10 (RXP[32]); also elsewhere on the board
/S08_SW_RX1_N: U1.AU9 (RXN[33]); also elsewhere on the board
/S08_SW_RX1_P: U1.AV9 (RXP[33]); also elsewhere on the board
/S08_SW_RX2_N: U1.AR8 (RXN[34]); also elsewhere on the board
/S08_SW_RX2_P: U1.AT8 (RXP[34]); also elsewhere on the board
/S08_SW_RX3_N: U1.AU7 (RXN[35]); also elsewhere on the board
/S08_SW_RX3_P: U1.AV7 (RXP[35]); also elsewhere on the board
/S09_SW_RX0_N: U1.AR6 (RXN[36]); also elsewhere on the board
/S09_SW_RX0_P: U1.AT6 (RXP[36]); also elsewhere on the board
/S09_SW_RX1_N: U1.AU5 (RXN[37]); also elsewhere on the board
/S09_SW_RX1_P: U1.AV5 (RXP[37]); also elsewhere on the board
/S09_SW_RX2_N: U1.AR4 (RXN[38]); also elsewhere on the board
/S09_SW_RX2_P: U1.AT4 (RXP[38]); also elsewhere on the board
/S09_SW_RX3_N: U1.AU3 (RXN[39]); also elsewhere on the board
/S09_SW_RX3_P: U1.AV3 (RXP[39]); also elsewhere on the board
/S10_SW_RX0_N: U1.AN6 (RXN[40]); also elsewhere on the board
/S10_SW_RX0_P: U1.AN5 (RXP[40]); also elsewhere on the board
/S10_SW_RX1_N: U1.AM8 (RXN[41]); also elsewhere on the board
/S10_SW_RX1_P: U1.AM7 (RXP[41]); also elsewhere on the board
/S10_SW_RX2_N: U1.AL6 (RXN[42]); also elsewhere on the board
/S10_SW_RX2_P: U1.AL5 (RXP[42]); also elsewhere on the board
/S10_SW_RX3_N: U1.AK8 (RXN[43]); also elsewhere on the board
/S10_SW_RX3_P: U1.AK7 (RXP[43]); also elsewhere on the board
/S10_SW_TX0_N: U1.AN2 (TXN[40]); also elsewhere on the board
/S10_SW_TX0_P: U1.AN1 (TXP[40]); also elsewhere on the board
/S10_SW_TX1_N: U1.AM3 (TXN[41]); also elsewhere on the board
/S10_SW_TX1_P: U1.AM2 (TXP[41]); also elsewhere on the board
/S10_SW_TX2_N: U1.AL2 (TXN[42]); also elsewhere on the board
/S10_SW_TX2_P: U1.AL1 (TXP[42]); also elsewhere on the board
/S10_SW_TX3_N: U1.AK3 (TXN[43]); also elsewhere on the board
/S10_SW_TX3_P: U1.AK2 (TXP[43]); also elsewhere on the board
/UP_TX0_P: U1.A26 (TXP[64]); also elsewhere on the board
/UP_TX2_P: U1.A24 (TXP[66]); also elsewhere on the board
